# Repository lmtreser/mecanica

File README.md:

# Dispositivos mecánicos

Colección de dispositivos y artilugios mecánicos para vincular con electrónica. 

La mayoría de los diseños fueron descargados desde el sitio web [Thingiverse](https://www.thingiverse.com/). Lea los archivos `README.txt` respectivos para más detalles.

## Modelos 3D

- `Archimedes screw` [tornillo de Arquímedes](https://es.wikipedia.org/wiki/Tornillo_de_Arqu%C3%ADmedes) para mover sólidos.
- `DIN rail/Arduino DIN rail clip & bumper` montaje en riel DIN para placa Arduino UNO.
- `DIN rail/Din Rail for mega 2560` montaje en riel DIN para placa Arduino MEGA 2560.
- `DIN rail/DIN-Rail Mount for Arduino Mega 2560` montaje en riel DIN para placa Arduino MEGA 2560.
- `DIN rail/ESP32 Lolin Din rail mount` montaje en riel DIN para placa ESP32 Lolin.
- `DIN rail/ESP8266 V3 vertical DIN rail` montaje en riel DIN para placa NodeMCU ESP8266.
- `Pilas 18650` portapilas desde 1 a 4 pilas recargables modelo 18650.
- `Roller Blind` mecanismos para cortina de enrollar motorizada.
- `Suspension Servo` mecanismo de suspensión y dirección delantera para robótica.
- `Tolva Servo SG90` tolva dosificadora de sólidos con servo modelo SG90.

## Ánexos Técnicos

- `Agujeros.pdf` Tabla diámetro de agujero a roscar, tipos de machos.
- `Catálogo_Bulones.pdf` Catálogo bulones, arandelas, tuercas, tornillos, espárragos y varillas.
- `Riel DIN.pdf` Breve apunte sobre el riel DIN.
- `Tipos de roscas.pdf` Tabla tipos de roscas.

## Objetos

Colección de objetos, componentes y dispositivos útiles para la confección de sistemas.

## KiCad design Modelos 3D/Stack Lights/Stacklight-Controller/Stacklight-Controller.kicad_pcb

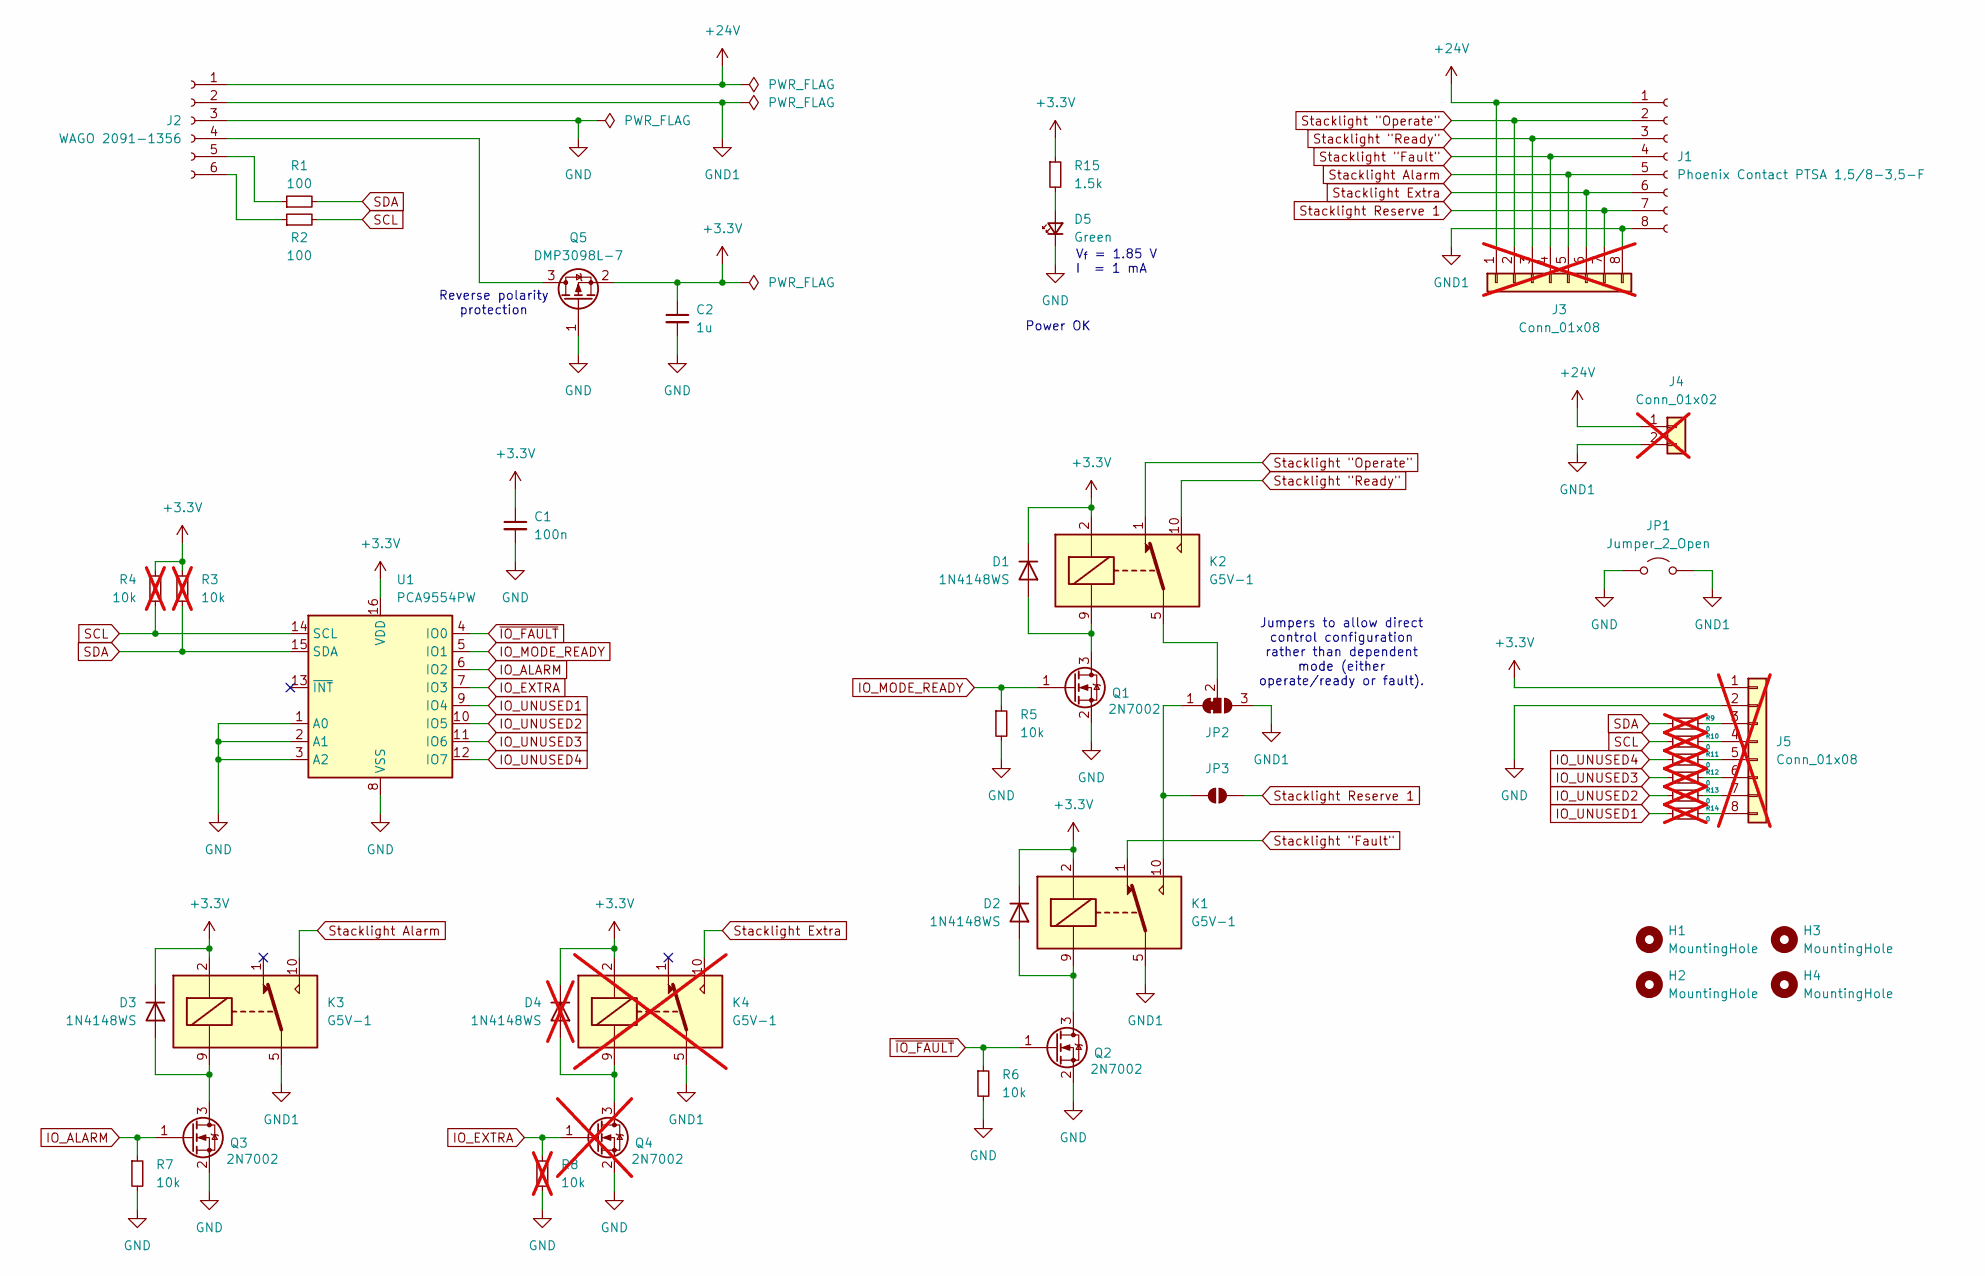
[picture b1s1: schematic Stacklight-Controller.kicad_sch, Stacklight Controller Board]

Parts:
C1: 100n; C_0603_1608Metric_Pad1.08x0.95mm_HandSolder
C2: 1u; C_0805_2012Metric_Pad1.18x1.45mm_HandSolder
D1, D2, D3: 1N4148WS; D_SOD-323_HandSoldering
D4: 1N4148WS; D_SOD-323_HandSoldering; not fitted
D5: Green; LED_0805_2012Metric_Pad1.15x1.40mm_HandSolder
H1, H2, H3, H4: MountingHole; MountingHole_3.2mm_M3
J1: Phoenix Contact PTSA 1,5/8-3,5-F; Phoenix_PTSA_1,5_8-3,5-F
J2: WAGO 2091-1356; WAGO_2091-1356
J3, J5: Conn_01x08; PinHeader_1x08_P2.54mm_Vertical; not fitted
J4: Conn_01x02; PinHeader_1x02_P2.54mm_Vertical; not fitted
JP1: Jumper_2_Open; PinHeader_1x02_P2.54mm_Vertical
JP2: SolderJumper_3_Bridged12; SolderJumper-3_P1.3mm_Open_RoundedPad1.0x1.5mm
JP3: SolderJumper_2_Open; SolderJumper-2_P1.3mm_Open_RoundedPad1.0x1.5mm
K1, K2, K3: G5V-1; Relay_SPDT_Omron_G5V-1
K4: G5V-1; Relay_SPDT_Omron_G5V-1; not fitted
Q1, Q2, Q3: 2N7002; SOT-23
Q4: 2N7002; SOT-23; not fitted
Q5: DMP3098L-7; SOT-23_Handsoldering
R1, R2: 100; R_0603_1608Metric_Pad0.98x0.95mm_HandSolder
R3, R4, R8: 10k; R_0603_1608Metric_Pad0.98x0.95mm_HandSolder; not fitted
R5, R6, R7: 10k; R_0603_1608Metric_Pad0.98x0.95mm_HandSolder
R9, R10, R11, R12, R13, R14: 0; R_0603_1608Metric_Pad0.98x0.95mm_HandSolder; not fitted
R15: 1.5k; R_0603_1608Metric_Pad0.98x0.95mm_HandSolder
U1: PCA9554PW; TSSOP-16_4.4x5mm_P0.65mm

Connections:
+3.3V: C1.1, C2.1, D1.1 (K), D2.1 (K), D3.1 (K), D4.1 (K), J5.1, K1.2, K2.2, K3.2, K4.2, Q5.2 (S), R3.1, R4.1, R15.1, U1.16 (VDD)
+24V: J1.1, J2.1, J3.1, J4.1
GND: C1.2, C2.2, D5.1 (K), J2.3, J5.2, JP1.1 (A), Q1.2 (S), Q2.2 (S), Q3.2 (S), Q4.2 (S), Q5.1 (G), R5.2, R6.2, R7.2, R8.2, U1.1 (A0), U1.2 (A1), U1.3 (A2), U1.8 (VSS)
GND1: J1.8, J2.2, J3.8, J4.2, JP1.2 (B), JP2.3 (B), K1.5, K1.6, K3.5, K3.6, K4.5, K4.6
IO_ALARM: Q3.1 (G), R7.1, U1.6 (IO2)
IO_EXTRA: Q4.1 (G), R8.1, U1.7 (IO3)
IO_MODE_READY: Q1.1 (G), R5.1, U1.5 (IO1)
IO_UNUSED1: R14.1, U1.9 (IO4)
IO_UNUSED2: R13.1, U1.10 (IO5)
IO_UNUSED3: R12.1, U1.11 (IO6)
IO_UNUSED4: R11.1, U1.12 (IO7)
unnamed: D1.2 (A), K2.9, Q1.3 (D)
unnamed: D2.2 (A), K1.9, Q2.3 (D)
unnamed: D3.2 (A), K3.9, Q3.3 (D)
unnamed: D4.2 (A), K4.9, Q4.3 (D)
unnamed: D5.2 (A), R15.2
unnamed: J2.4, Q5.3 (D)
unnamed: J2.5, R1.1
unnamed: J2.6, R2.1
unnamed: J5.3, R9.2
unnamed: J5.4, R10.2
unnamed: J5.5, R11.2
unnamed: J5.6, R12.2
unnamed: J5.7, R13.2
unnamed: J5.8, R14.2
unnamed: JP2.1 (A), JP3.1 (A), K1.10
unnamed: JP2.2 (C), K2.5, K2.6
SCL: R2.2, R4.2, R10.1, U1.14 (SCL)
SDA: R1.2, R3.2, R9.1, U1.15 (SDA)
Stacklight "Fault": J1.4, J3.4, K1.1
Stacklight "Operate": J1.2, J3.2, K2.1
Stacklight "Ready": J1.3, J3.3, K2.10
Stacklight Alarm: J1.5, J3.5, K3.10
Stacklight Extra: J1.6, J3.6, K4.10
Stacklight Reserve 1: J1.7, J3.7, JP3.2 (B)
~IO_FAULT: Q2.1 (G), R6.1, U1.4 (IO0)

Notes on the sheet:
Jumpers to allow direct control configuration rather than dependent mode (either operate/ready or fault).
Power OK
V_{f} = 1.85 V I = 1 mA
Reverse polarity protection

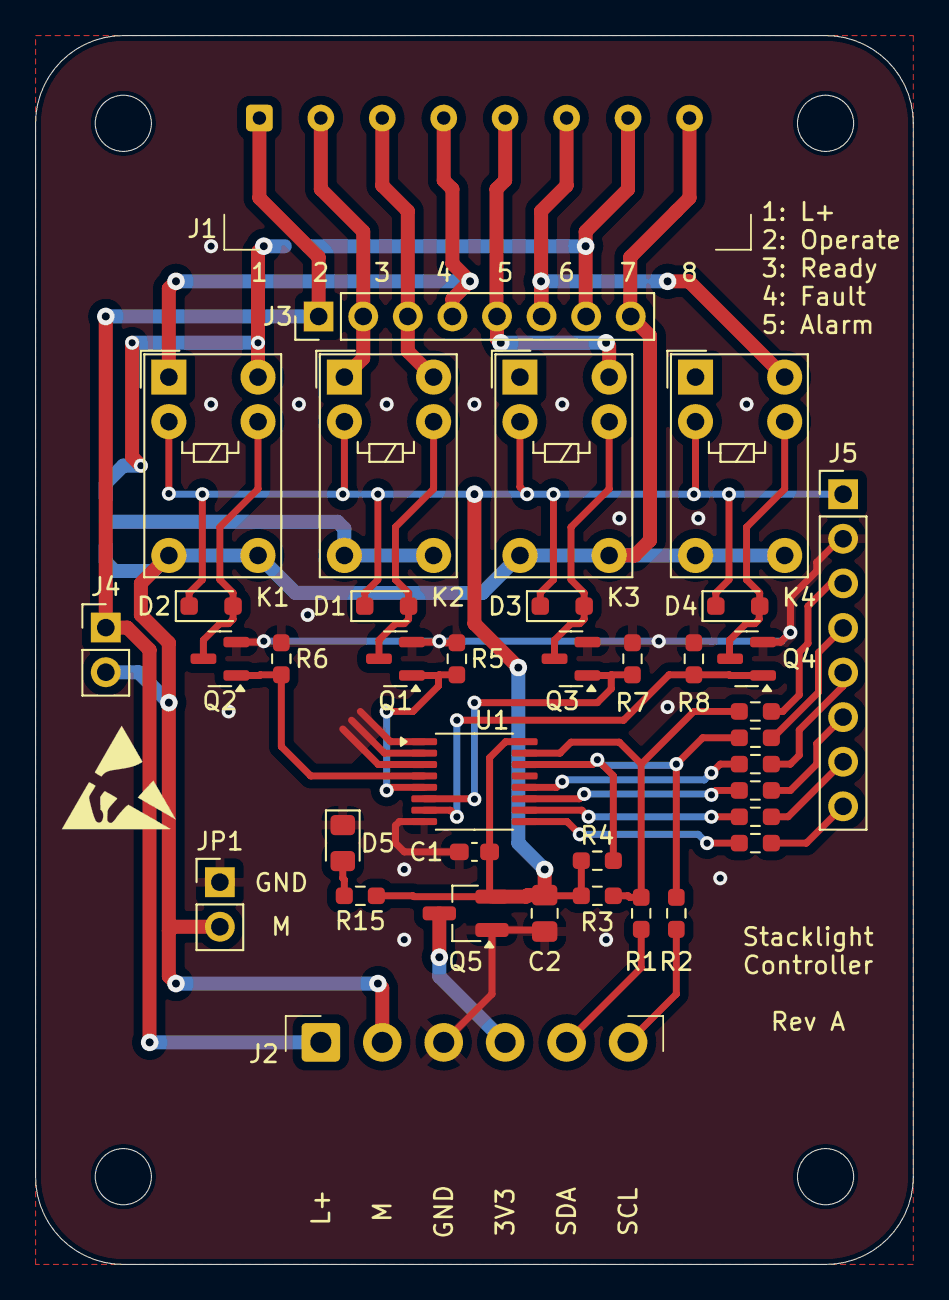
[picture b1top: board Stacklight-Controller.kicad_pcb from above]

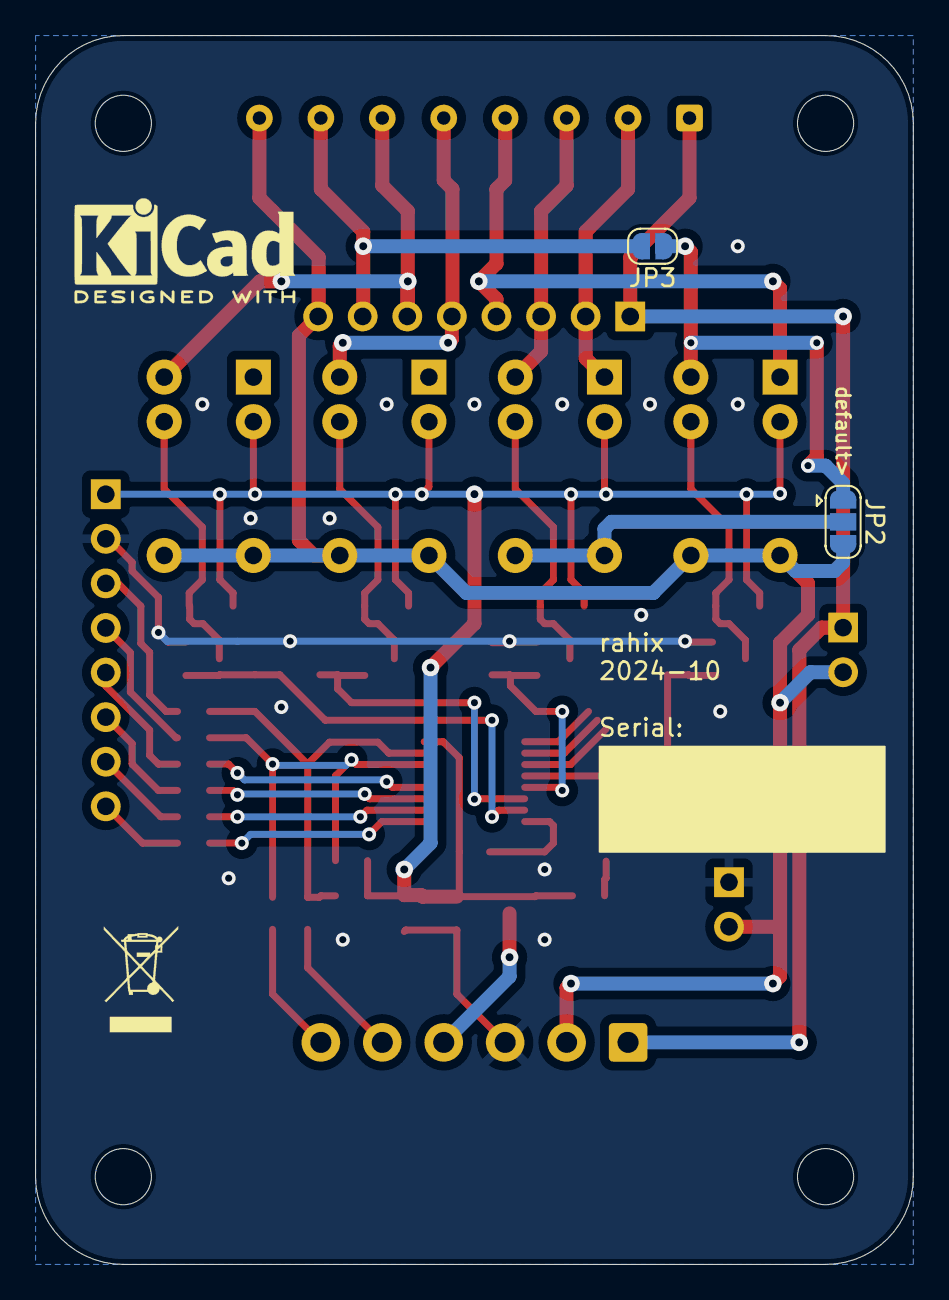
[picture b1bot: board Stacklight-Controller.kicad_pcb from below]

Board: 2 copper layers, 50.0 x 70.0 mm, 44 parts (2 on the bottom side), 36 nets.

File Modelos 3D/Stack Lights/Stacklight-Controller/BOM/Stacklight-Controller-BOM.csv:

"Qty","Reference","Value","Footprint","DNP"
"1","J1","Phoenix Contact PTSA 1,5/8-3,5-F","0_Local_Library:Phoenix_PTSA_1,5_8-3,5-F",""
"1","J2","WAGO 2091-1356","0_Local_Library:WAGO_2091-1356",""
"1","C1","100n","Capacitor_SMD:C_0603_1608Metric_Pad1.08x0.95mm_HandSolder",""
"1","C2","1u","Capacitor_SMD:C_0805_2012Metric_Pad1.18x1.45mm_HandSolder",""
"1","JP1","Jumper_2_Open","Connector_PinHeader_2.54mm:PinHeader_1x02_P2.54mm_Vertical",""
"3","D1,D2,D3","1N4148WS","Diode_SMD:D_SOD-323_HandSoldering",""
"1","D5","Green","LED_SMD:LED_0805_2012Metric_Pad1.15x1.40mm_HandSolder",""
"1","U1","PCA9554PW","Package_SO:TSSOP-16_4.4x5mm_P0.65mm",""
"3","Q1,Q2,Q3","2N7002","Package_TO_SOT_SMD:SOT-23",""
"1","Q5","DMP3098L-7","Package_TO_SOT_SMD:SOT-23_Handsoldering",""
"3","K1,K2,K3","G5V-1","Relay_THT:Relay_SPDT_Omron_G5V-1",""
"2","R1,R2","100","Resistor_SMD:R_0603_1608Metric_Pad0.98x0.95mm_HandSolder",""
"3","R5,R6,R7","10k","Resistor_SMD:R_0603_1608Metric_Pad0.98x0.95mm_HandSolder",""
"1","R15","1.5k","Resistor_SMD:R_0603_1608Metric_Pad0.98x0.95mm_HandSolder",""

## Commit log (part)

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2023-11-23 Cortina tipo Roller
2023-11-23 Suspension delantera con servo
2023-11-23 Tolva con servo SG90
2023-12-02 Portapilas 18650
2024-02-03 Actualizar README.md
2024-02-03 update repo
2024-02-03 remove file
2024-02-08 update Arduino DIN Rail
2024-02-08 update DIN Rail
2024-02-08 add ESP8266/ESP32 DIN rail
2024-02-08 add tornillo de arquimedes
2024-02-12 org dir
2024-02-12 add tornilleria
2024-02-14 update ánexos técnicos
2024-02-22 add Riel DIN
2024-05-08 add Motorreductor Robótica
2024-05-17 add rueda loca
2024-05-26 add separador de 30mm para tornillos M3
2024-06-04 add box generator
2024-06-04 add turbocase
2024-06-25 add riel din model
2024-07-12 add smart home models
2024-08-07 update stl
2024-08-16 add tablet stand
2024-08-19 add motor
2024-08-19 add DIN Rail Cable Clamp
2024-08-19 add DIN Rail Stand
2024-08-19 add GmM USB to RS485 transceiver DIN case
2024-08-19 add DIN Rail Mount
2024-08-19 add Raspberry Pi 3B+ Din-Rail Mount
2024-08-19 add Raspberry Pi B+ Raspberry Pi 2 Din-Rail Mount
2024-08-22 add Zero Din Rail
2024-08-22 add DIN Mount Template With Component Examples
2024-08-27 add LM2596S DIN Rail
2024-08-27 add DIN Rail Holder
2024-08-27 add Power Switch Tray
2024-09-04 add meccano pieces
2024-10-14 add Arduino Uno Bumper
2024-10-29 add rotary encoder wheel
2025-01-31 add examples, courses
2025-01-31 add news models
2025-04-04 add openscad libs
2025-04-04 add examples
2025-04-04 add openscad tutorial
2025-04-18 add nuts&bolts datasheets
2025-05-05 add Five hundred and seven mechanical movements book
2025-05-05 add Stack Lights
2025-05-05 add tips 3d printing
2025-05-05 add 22mm Label Carrier
2025-05-05 22mm Blind Plug
2025-05-05 add Terminal Marker Strip Phoenix PT-Series
2025-05-05 add Terminal Marker Strip Wago-280
2025-05-05 add Parametric Cable Strain Relief Plate
2025-05-05 add 22mm Button Indicator Label Carrier
2025-05-05 add DIN Rail Cable Comb
2025-05-05 add Barrel Jack Adapter DIN Rail Mount
2025-05-05 add DIN Rail Wiring System
2025-06-27 add 817 module
2025-07-09 add dune3d projects
2025-07-09 add 18650 pack x3
2025-07-09 add simple part tutorial
2025-07-09 add sample case
2025-07-09 add first project example
2025-07-09 update project
2025-07-09 add readme
2025-07-09 update first project
2025-07-09 update from photo
2025-07-10 update from photo project
2025-07-19 update projects
2025-07-24 din rail mount template
2025-07-25 update template
2025-07-25 add esp01 rele module
2025-08-01 add torx screws
2025-08-12 add riel din template
2025-08-13 update model
2025-09-08 add ejercicios freecad
2025-10-03 add micro motor mount
2025-11-01 add Riel DIN Nano+RS485
2026-05-27 add terminal block 3d models
